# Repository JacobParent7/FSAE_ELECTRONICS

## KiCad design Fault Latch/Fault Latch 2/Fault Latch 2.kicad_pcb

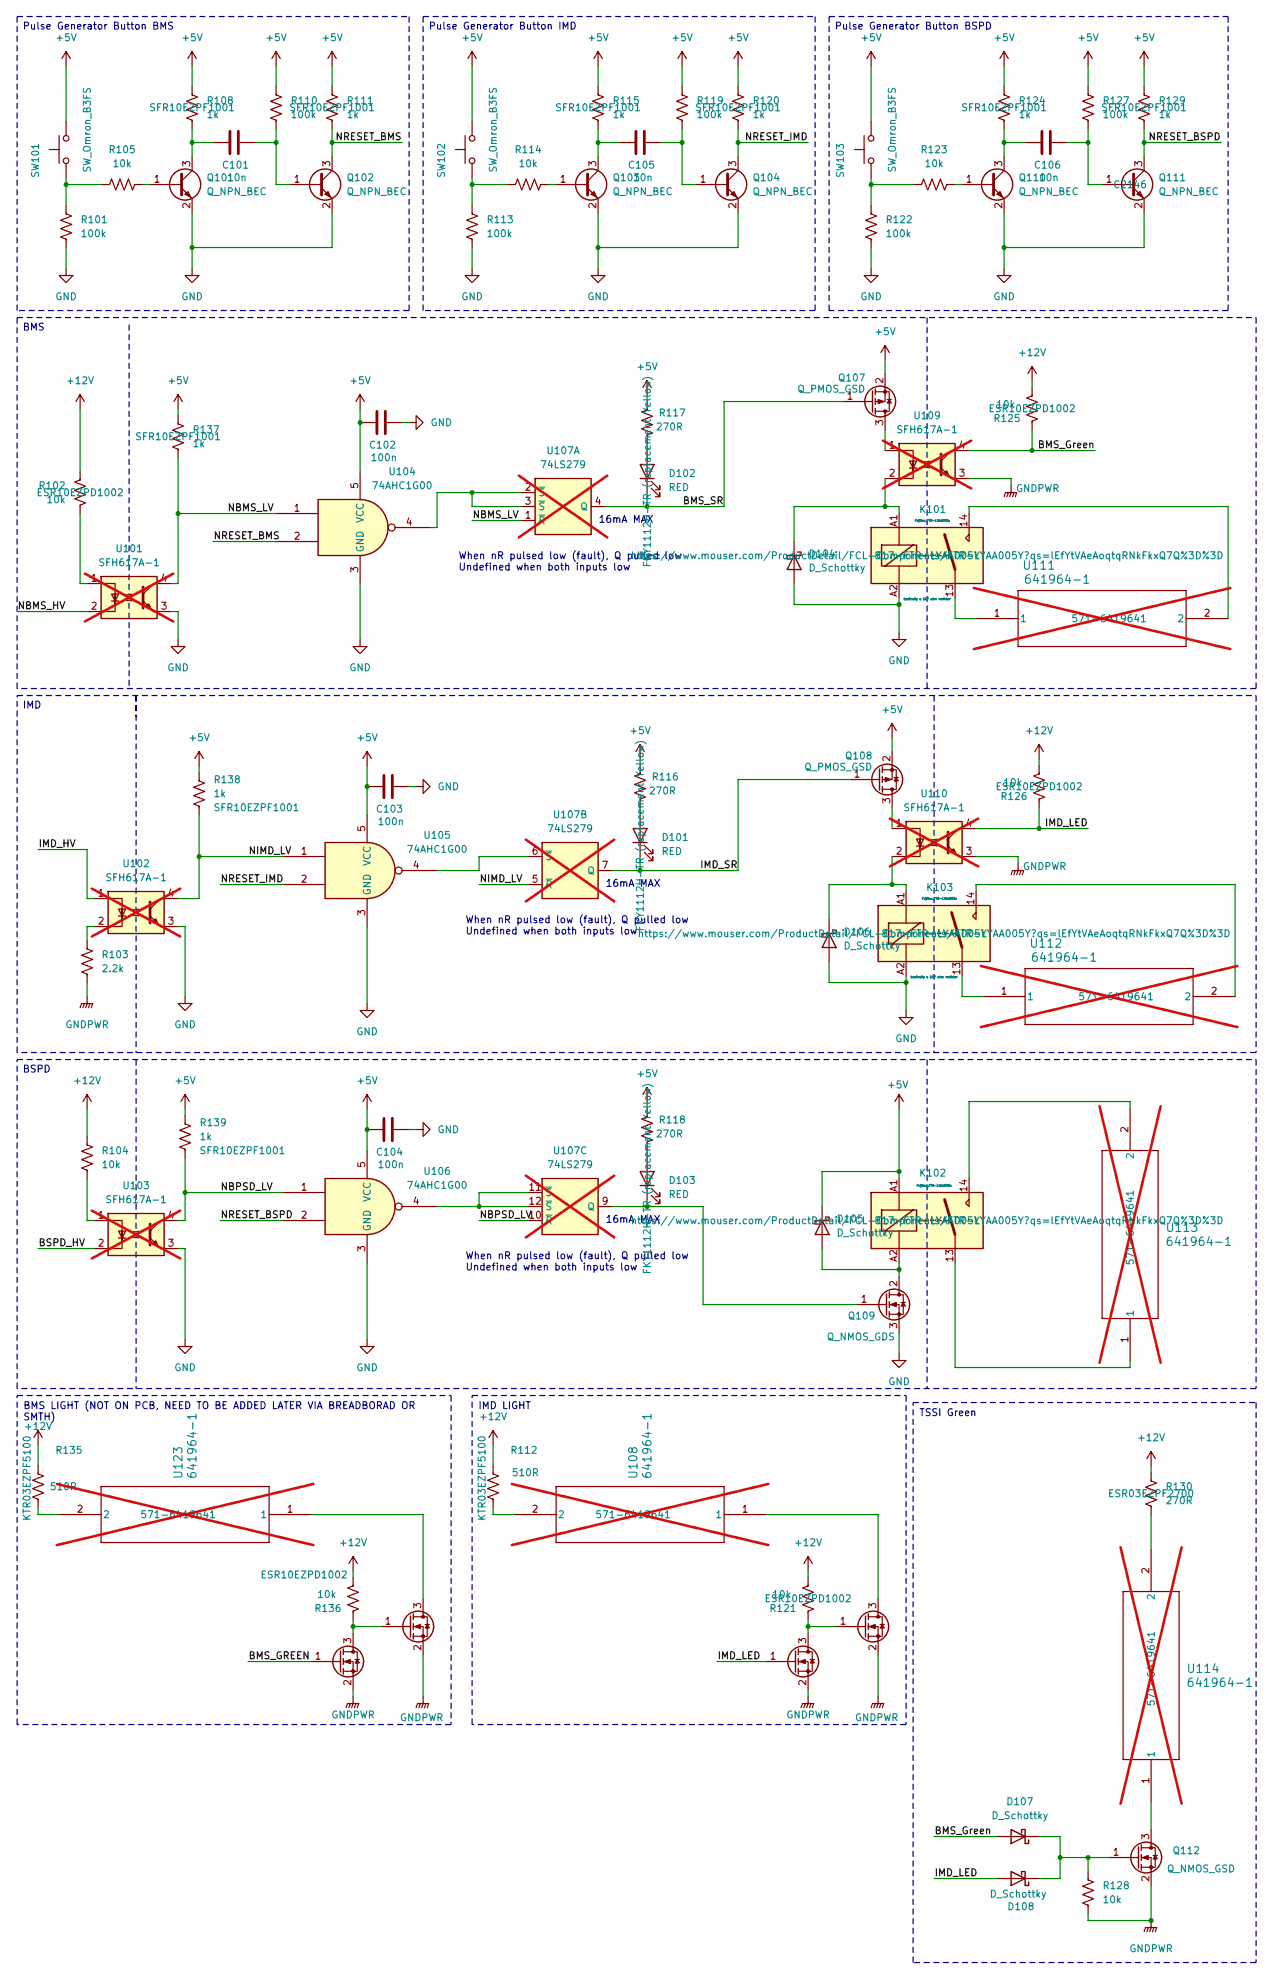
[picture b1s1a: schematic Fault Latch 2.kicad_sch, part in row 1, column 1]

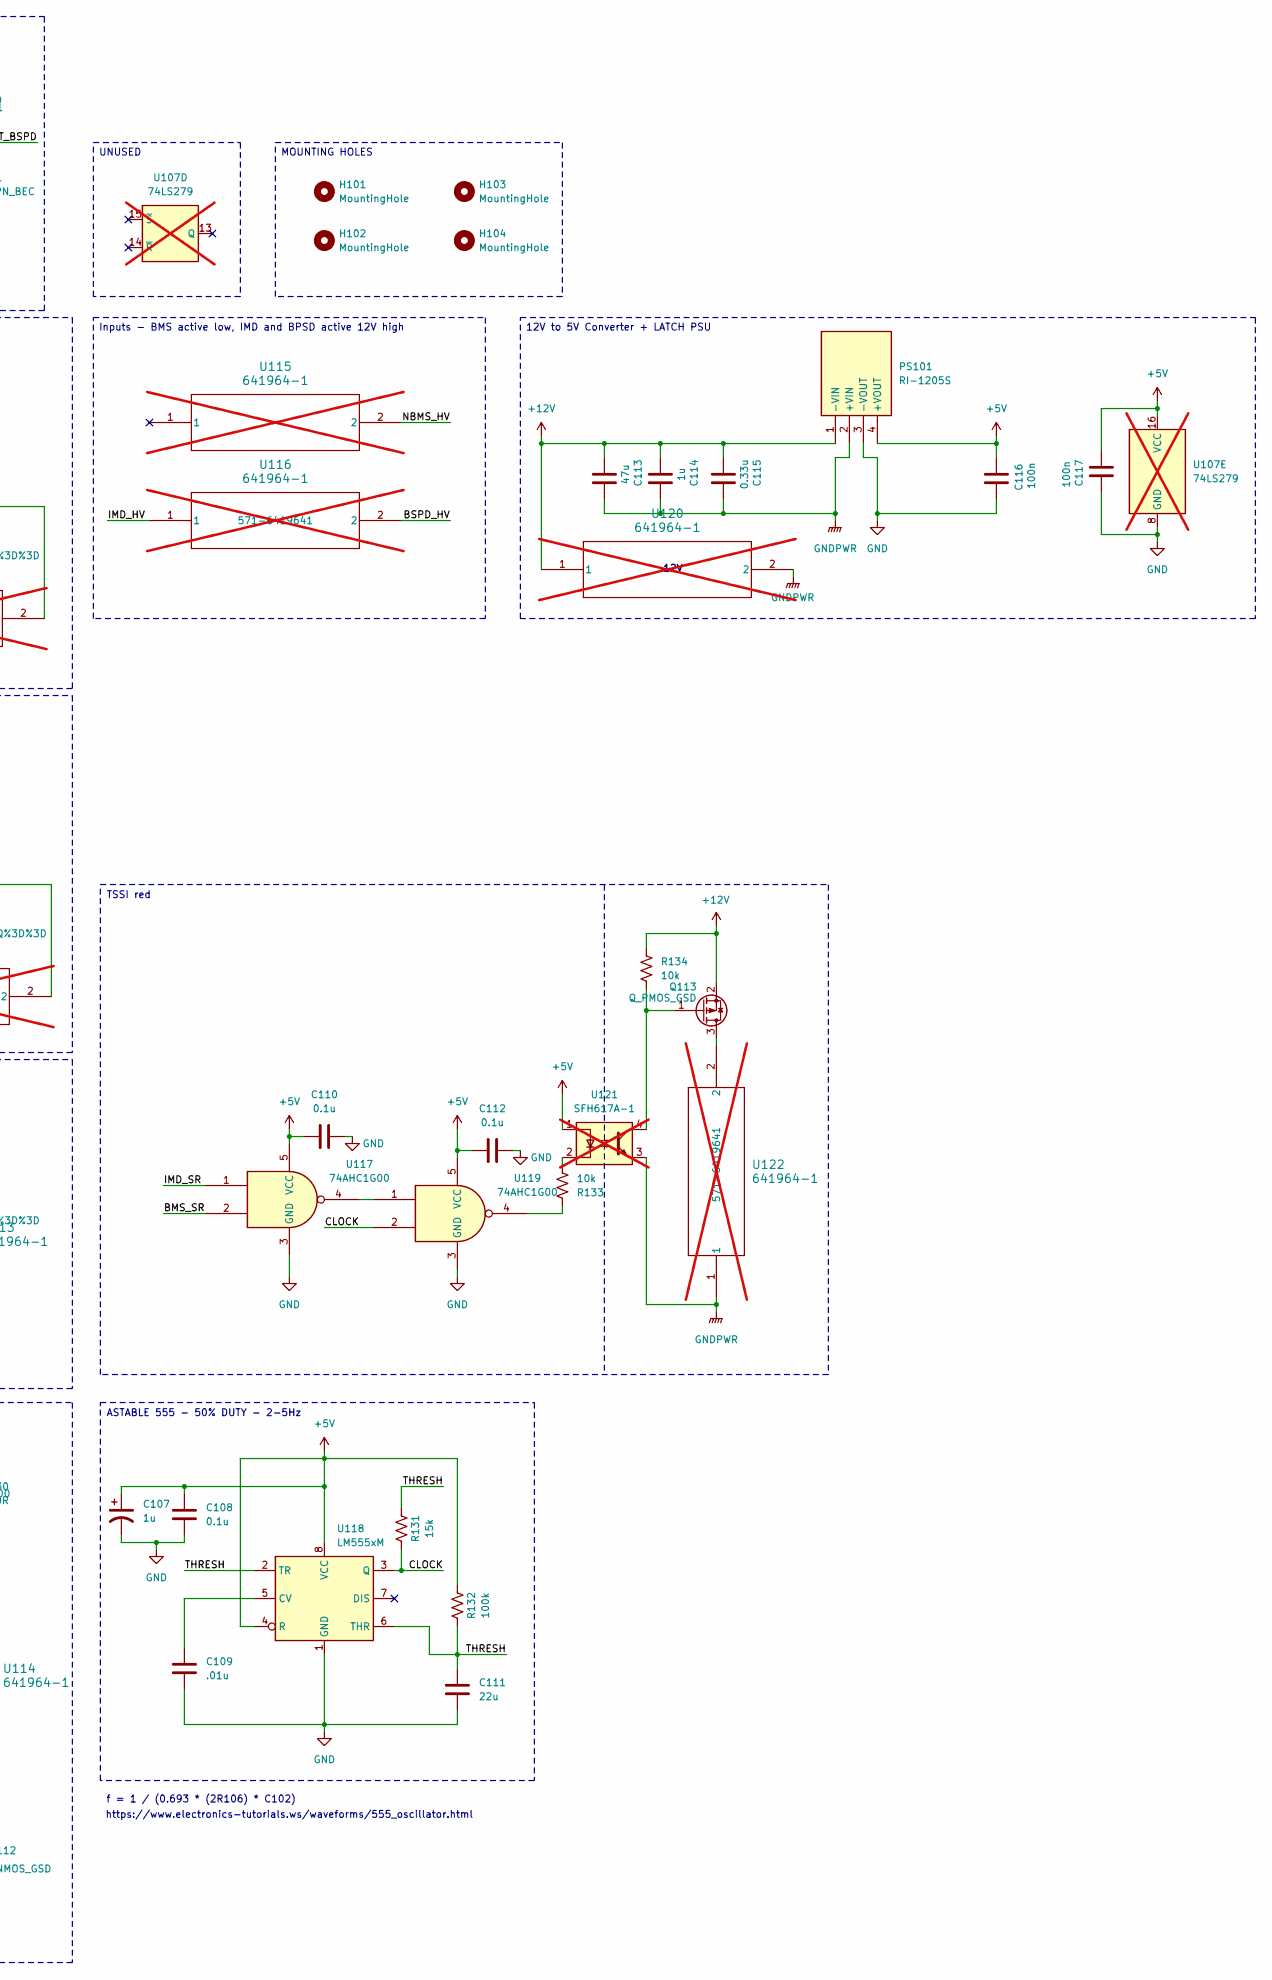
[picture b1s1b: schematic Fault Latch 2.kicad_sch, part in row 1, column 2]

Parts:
C101, C105, C106: 10n; C_0603_1608Metric_Pad1.08x0.95mm_HandSolder; JLC# C1589
C102, C103, C104, C116, C117: 100n; C_0603_1608Metric_Pad1.08x0.95mm_HandSolder; JLC# C1591
C107: 1u; C_0402_1005Metric; JLC# C59782
C108, C110, C112: 0.1u; C_0402_1005Metric; JLC# C133086
C109: .01u; C_0402_1005Metric; JLC# C15195
C111: 22u; C_0402_1005Metric; JLC# C105226
C113: 47u; CP_Elec_6.3x5.4; JLC# C2836440
C114: 1u; C_0805_2012Metric_Pad1.18x1.45mm_HandSolder; JLC# C91186
C115: 0.33u; C_0603_1608Metric_Pad1.08x0.95mm_HandSolder; JLC# C282682
D101, D102, D103: RED; LED_0805_2012Metric_Pad1.15x1.40mm_HandSolder; JLC# C19171391
D104, D105, D106, D107, D108: D_Schottky; D_SMA; JLC# C8678
H101, H102, H103, H104: MountingHole; MountingHole_3.2mm_M3
K101, K102, K103: Fujitsu_FTR-LYAA005x; Relay_SPST-NO_Fujitsu_FTR-LYAA005x_FormA_Vertical; MOUSER 817-FTR-LYAA005Y
PS101: RI-1205S; RI0505S; Mouser Part Number 919-RI-1205S
Q101, Q102, Q103, Q104, Q110, Q111: Q_NPN_BEC; SOT-23; JLC# C2146
Q105, Q106, Q112, Q114, Q115: Q_NMOS_GSD; SOT-23; JLC# C151421
Q107, Q108, Q113: Q_PMOS_GSD; SOT-523; JLC# C96676
Q109: Q_NMOS_GDS; TO-252-2; JLC# C2889156
R101, R110, R113, R119, R122, R127: 100k; R_0805_2012Metric_Pad1.20x1.40mm_HandSolder; JLC# C149504
R102, R121, R125, R126, R136: 10k; R_0805_2012Metric_Pad1.20x1.40mm_HandSolder; MOUSER ESR10EZPD1002
R103: 2.2k; R_0805_2012Metric_Pad1.20x1.40mm_HandSolder; JLC# C17520
R104, R105, R114, R123: 10k; R_0805_2012Metric_Pad1.20x1.40mm_HandSolder; JLC# C17414
R108, R111, R115, R120, R124, R129, R137, R138, R139: 1k; R_0805_2012Metric_Pad1.20x1.40mm_HandSolder; JLC# C17513
R112, R135: 510R; R_0603_1608Metric; MOUSER KTR03EZPF5100
R116, R117, R118: 270R; R_0805_2012Metric_Pad1.20x1.40mm_HandSolder; JLC# C17590
R128: 10k; R_0603_1608Metric; JLC# C130232
R130: 270R; R_0603_1608Metric; MOUSER ESR03EZPF2700
R131: 15k; R_0603_1608Metric; JLC# C22809
R132: 100k; R_0603_1608Metric; JLC# C60491
R133, R134: 10k; R_0603_1608Metric; JLC# C105637
SW101, SW102, SW103: SW_Omron_B3FS; SW_SPST_Omron_B3FS-100xP; JLC# C271750
U101, U102, U103, U109, U110, U121: SFH617A-1; DIP-4_W7.62mm; MOUSER SFH617A-1X007T; not fitted
U104, U105, U106, U117, U119: 74AHC1G00; SOT-23-5; JLC# C350556
U107: 74LS279; SOIC-16_3.9x9.9mm_P1.27mm; MOUSER 595-SN74LS279ADR; not fitted
U108, U111, U112, U113, U114, U115, U116, U120, U122, U123: 641964-1; TE_641964-1; MOUSER 571-6419641; not fitted
U118: LM555xM; SOIC-8_3.9x4.9mm_P1.27mm; JLC# C90760

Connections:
+5V: C102.1, C103.1, C104.1, C107.1, C108.1, C110.2, C112.2, C116.2, C117.1, D105.1 (K), K102.A1, PS101.4 (+VOUT), Q107.2 (S), Q108.2 (S), R108.1, R110.1, R111.1, R115.1, R116.2, R117.2, R118.2, R119.1, R120.1, R124.1, R127.1, R129.1, R132.2, R137.1, R138.2, R139.2, SW101.2, SW102.2, SW103.2, U104.5 (VCC), U105.5 (VCC), U106.5 (VCC), U107.16 (VCC), U117.5 (VCC), U118.4 (R), U118.8 (VCC), U119.5 (VCC), U121.1; also elsewhere on the board
+12V: C113.2, C114.2, C115.2, PS101.1 (-VIN), Q113.2 (S), R102.2, R104.2, R112.1, R121.1, R125.1, R126.1, R130.2, R134.1, R135.1, R136.1, U120.1
/BMS_Green: D107.2 (A), R125.2, U109.4
/BMS_SR: D102.1 (K), Q107.1 (G), U107.4 (Q), U117.2
/BSPD_HV: U103.2, U116.2
/CLOCK: R131.1, U118.3 (Q), U119.2
/IMD_HV: U102.1, U116.1
/IMD_LED: D108.2 (A), Q105.1 (G), R126.2, U110.4
/IMD_SR: D101.1 (K), Q108.1 (G), U107.7 (Q), U117.1
/NBMS_HV: U101.2, U115.2
/NBMS_LV: R137.2, U101.4, U104.1, U107.1 (~R); also elsewhere on the board
/NBPSD_LV: R139.1, U103.4, U106.1, U107.10 (~R); also elsewhere on the board
/NIMD_LV: R138.1, U102.4, U105.1, U107.5 (~R); also elsewhere on the board
/NRESET_BMS: Q102.3 (C), R111.2, U104.2
/NRESET_BSPD: Q111.3 (C), R129.2, U106.2
/NRESET_IMD: Q104.3 (C), R120.2, U105.2
/THRESH: C111.2, R131.2, R132.1, U118.2 (TR), U118.6 (THR)
GND: C102.2, C103.2, C104.2, C107.2, C108.2, C109.2, C110.1, C111.1, C112.1, C116.1, C117.2, D104.2 (A), D106.2 (A), K101.A2, K103.A2, PS101.3 (-VOUT), Q101.2 (E), Q102.2 (E), Q103.2 (E), Q104.2 (E), Q109.3 (S), Q110.2 (E), Q111.2 (E), R101.2, R113.2, R122.2, U101.3, U102.3, U103.3, U104.3 (GND), U105.3 (GND), U106.3 (GND), U107.8 (GND), U117.3 (GND), U118.1 (GND), U119.3 (GND)
GNDPWR: C113.1, C114.1, C115.1, PS101.2 (+VIN), Q105.2 (S), Q106.2 (S), Q112.2 (S), Q114.2 (S), Q115.2 (S), R103.2, R128.1, U109.3, U110.3, U120.2, U121.3, U122.1
unnamed: D101.2 (A), R116.1
unnamed: D102.2 (A), R117.1
unnamed: D103.2 (A), R118.1
unnamed: D103.1 (K), Q109.1 (G), U107.9 (Q)
unnamed: D104.1 (K), K101.A1, U109.2
unnamed: D105.2 (A), K102.A2, Q109.2 (D)
unnamed: D106.1 (K), K103.A1, U110.2
unnamed: D107.1 (K), D108.1 (K), Q112.1 (G), R128.2
unnamed: K101.13, U111.1
unnamed: K101.14, U111.2
unnamed: K102.13, U113.1
unnamed: K102.14, U113.2
unnamed: K103.13, U112.1
unnamed: K103.14, U112.2
unnamed: Q101.1 (B), R105.1
unnamed: C101.1, Q101.3 (C), R108.2
unnamed: C101.2, Q102.1 (B), R110.2
unnamed: Q103.1 (B), R114.1
unnamed: C105.1, Q103.3 (C), R115.2
unnamed: C105.2, Q104.1 (B), R119.2
unnamed: Q105.3 (D), Q106.1 (G), R121.2
unnamed: Q106.3 (D), U108.1
unnamed: Q107.3 (D), U109.1
unnamed: Q108.3 (D), U110.1
unnamed: Q110.1 (B), R123.1
unnamed: C106.1, Q110.3 (C), R124.2
unnamed: C106.2, Q111.1 (B), R127.2
unnamed: Q112.3 (D), U114.1
unnamed: Q113.3 (D), U122.2
unnamed: Q113.1 (G), R134.2, U121.4
unnamed: Q114.3 (D), Q115.1 (G), R136.2
unnamed: Q115.3 (D), U123.1
unnamed: R101.1, R105.2, SW101.1
unnamed: R102.1, U101.1
unnamed: R103.1, U102.2
unnamed: R104.1, U103.1
unnamed: R112.2, U108.2
unnamed: R113.1, R114.2, SW102.1
unnamed: R122.1, R123.2, SW103.1
unnamed: R130.1, U114.2
unnamed: R133.1, U121.2
unnamed: R133.2, U119.4
unnamed: R135.2, U123.2
unnamed: U104.4, U107.2 (~S), U107.3 (~S)
unnamed: U106.4, U107.11 (~S), U107.12 (~S)
unnamed: U105.4, U107.6 (~S)
unnamed: U117.4, U119.1
unnamed: C109.1, U118.5 (CV)

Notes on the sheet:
16mA MAX
12V
When nR pulsed low (fault), Q pulled low Undefined when both inputs low
f = 1 / (0.693 * (2R106) * C102)
https://www.electronics-tutorials.ws/waveforms/555_oscillator.html
UNUSED
BMS
Pulse Generator Button BMS
TSSI red
Pulse Generator Button BSPD
TSSI Green
ASTABLE 555 - 50% DUTY - 2-5Hz
Pulse Generator Button IMD
12V to 5V Converter + LATCH PSU
MOUNTING HOLES
Inputs - BMS active low, IMD and BPSD active 12V high
BMS LIGHT (NOT ON PCB, NEED TO BE ADDED LATER VIA BREADBORAD OR SMTH)
IMD
BSPD
IMD LIGHT

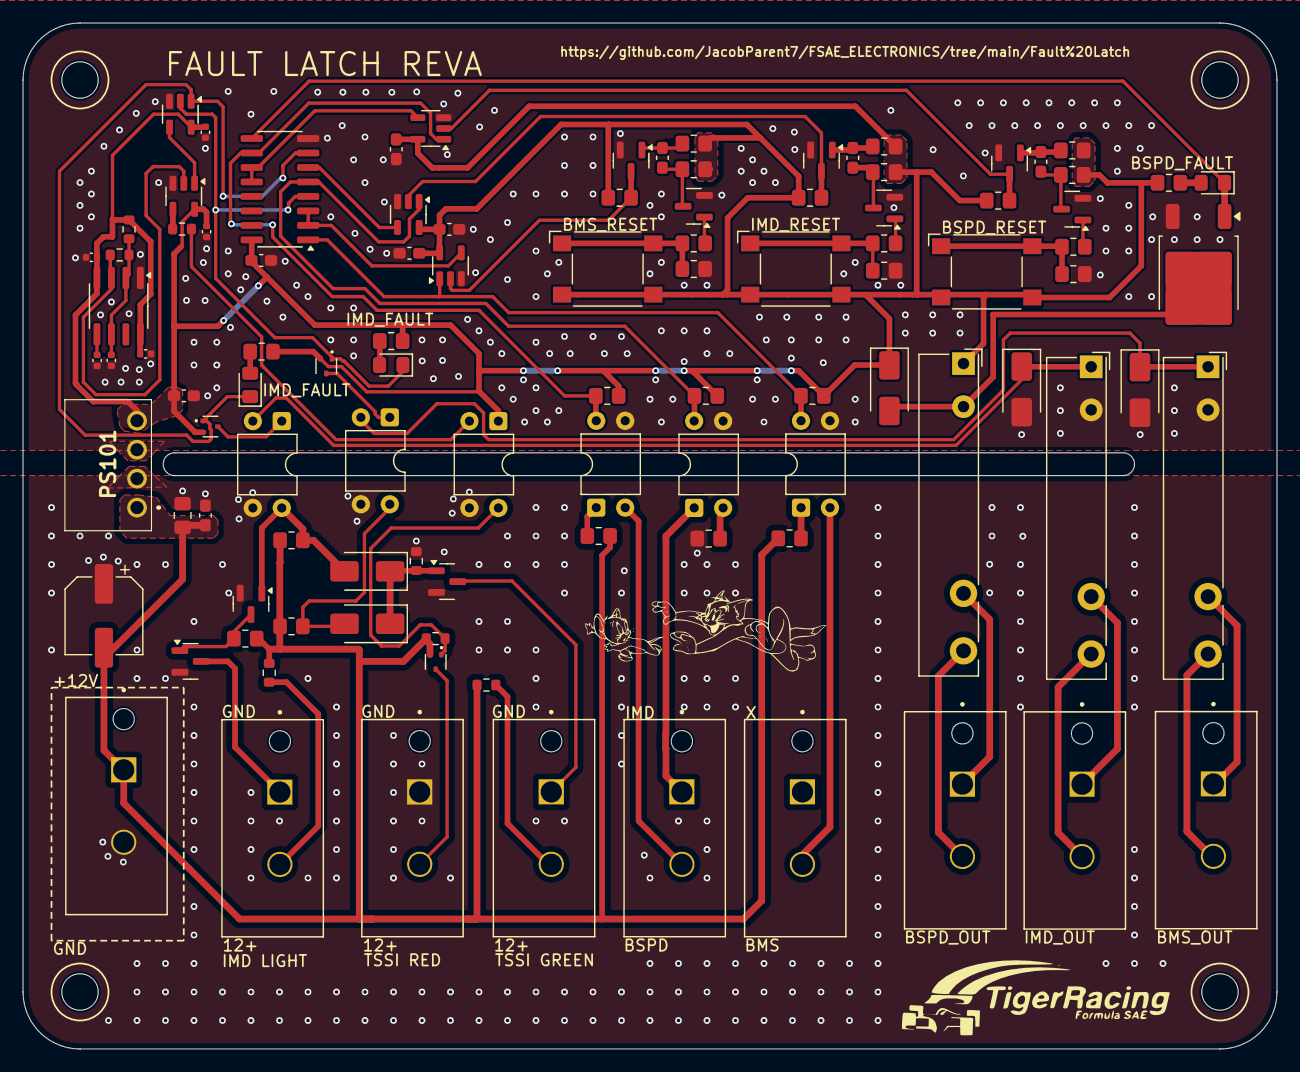
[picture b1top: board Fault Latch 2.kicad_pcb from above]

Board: 2 copper layers, 110.0 x 90.0 mm, 105 parts (0 on the bottom side), 64 nets.

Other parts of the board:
R106, R107, R109: 10k; R_0805_2012Metric_Pad1.20x1.40mm_HandSolder

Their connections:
+5V: R106.1, R107.1, R109.1; also elsewhere on the board
/NBMS_LV: R106.2; also elsewhere on the board
/NBPSD_LV: R107.2; also elsewhere on the board
/NIMD_LV: R109.2; also elsewhere on the board

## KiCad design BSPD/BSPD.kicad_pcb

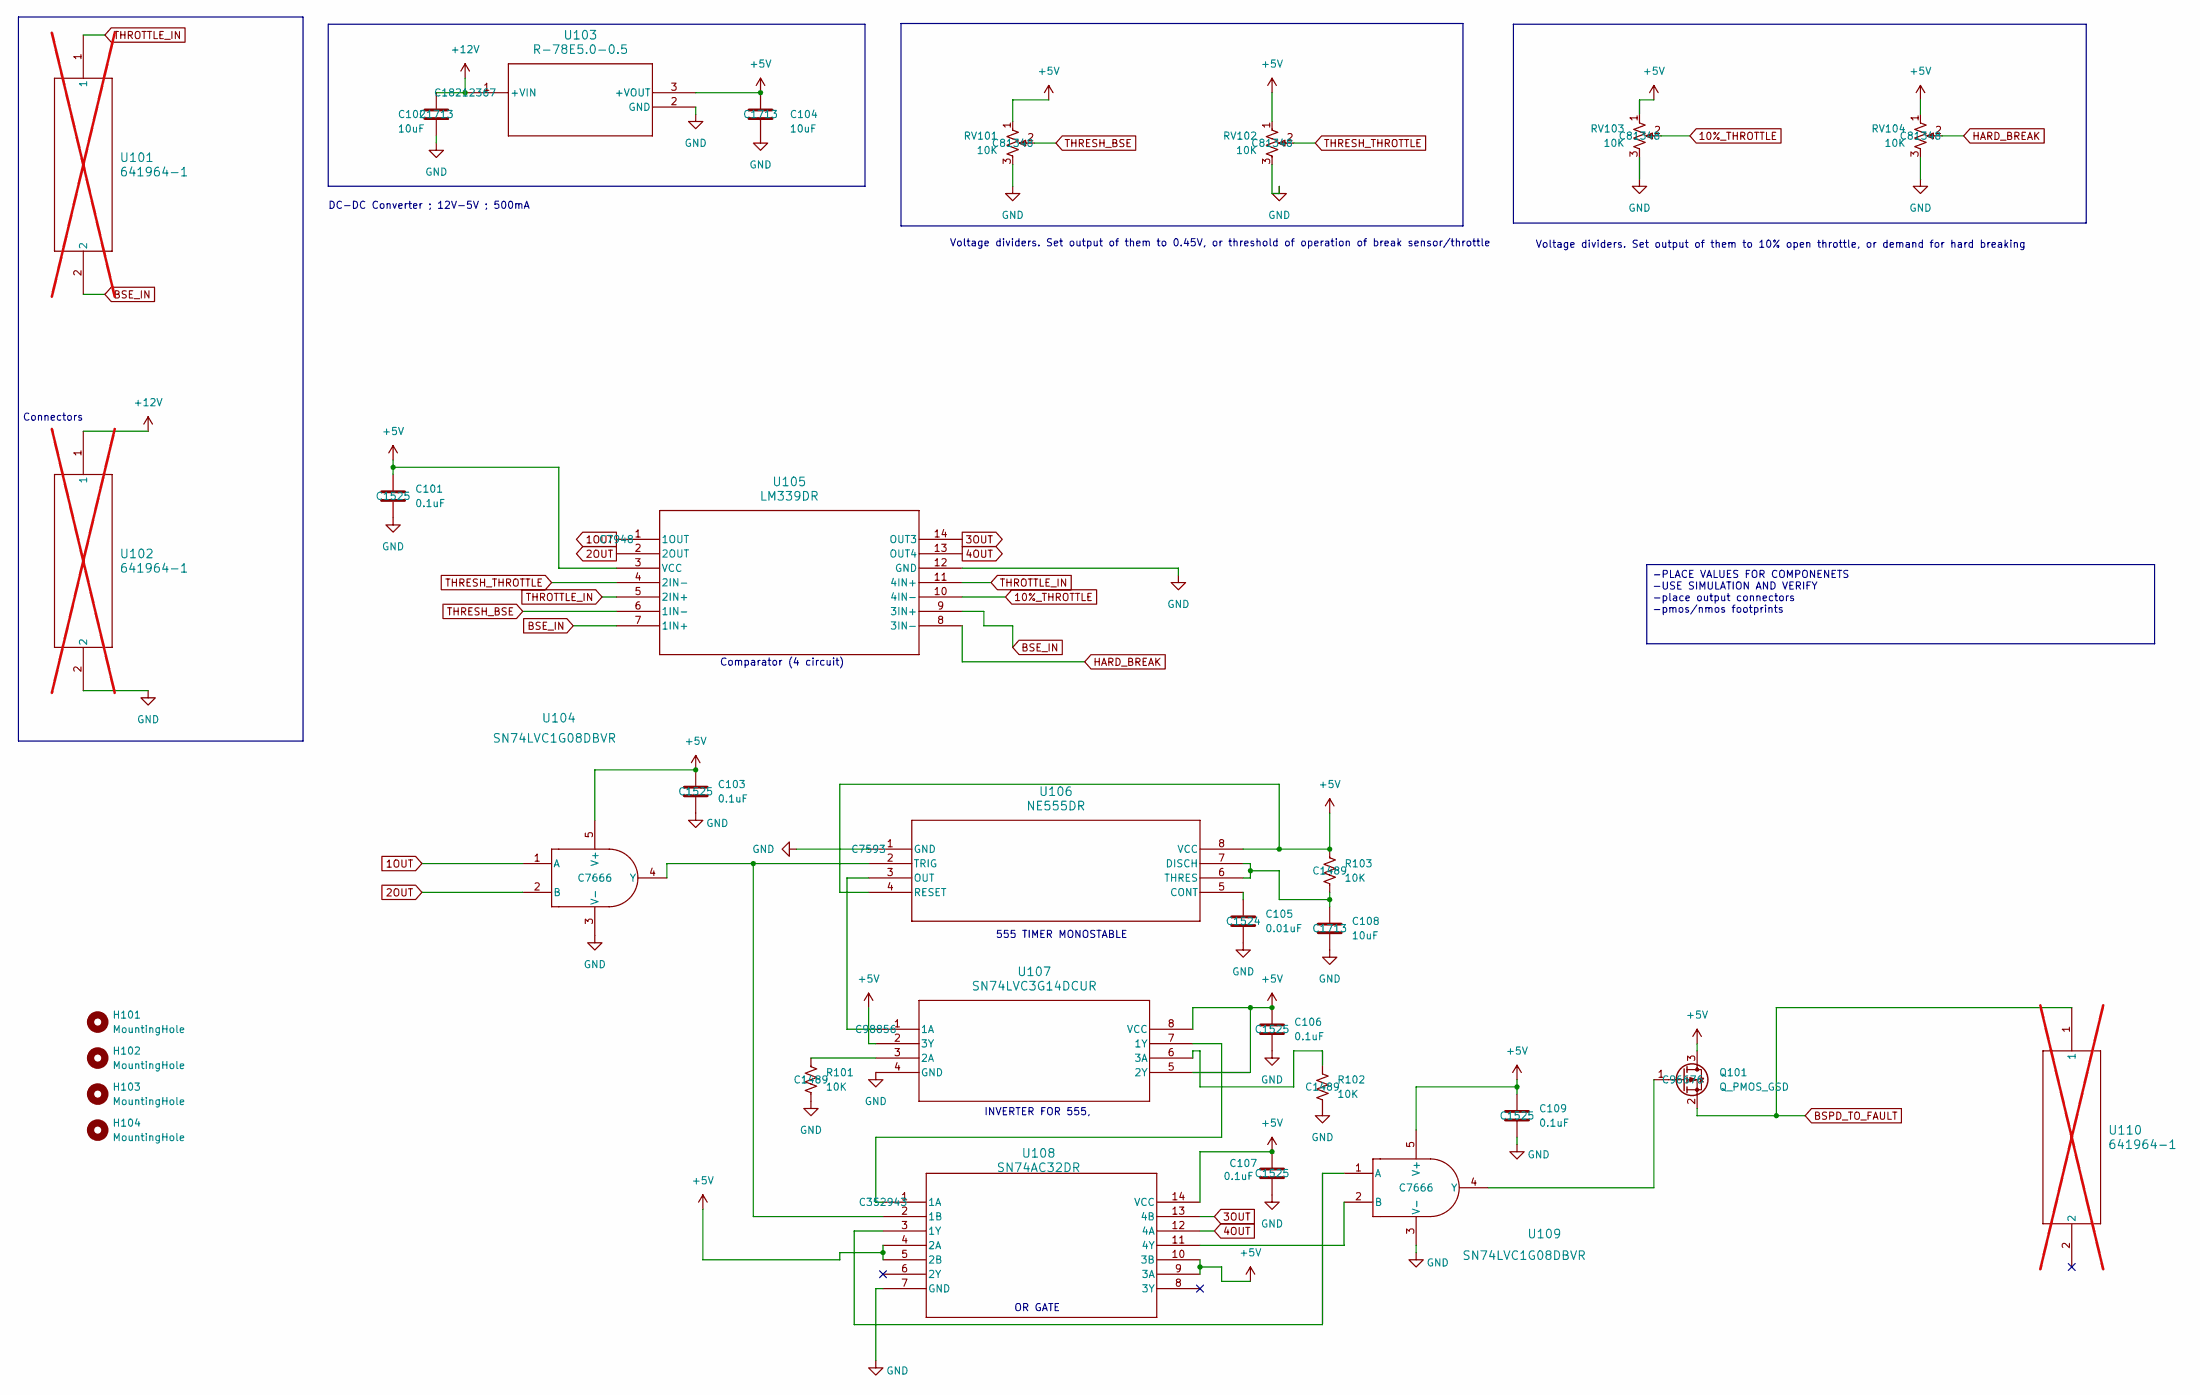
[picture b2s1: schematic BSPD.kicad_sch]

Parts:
C101, C103, C106, C107, C109: 0.1uF; C_0402_1005Metric; JLCPCB Part # C1525
C102, C104, C108: 10uF; C_0805_2012Metric; JLCPCB Part # C1713
C105: 0.01uF; C_0402_1005Metric; JLCPCB Part # C1524
H101, H102, H103, H104: MountingHole; MountingHole_2.2mm_M2
Q101: Q_PMOS_GSD; SOT-523; JLCPCB Part # C96676
R101, R102, R103: 10K; R_1206_3216Metric; JLCPCB Part # C1489
RV101, RV102, RV103, RV104: 10K; POT_3224W; JLCPCB Part # C81348
U101, U102, U110: 641964-1; 641964-1_TYC; not fitted
U103: R-78E5.0-0.5; R-78E-0.5_RCP; JLCPCB Part # C18212367
U104, U109: SN74LVC1G08DBVR; DBV0005A_L; JLCPCB Part # C7666
U105: LM339DR; D14; JLCPCB Part # C7948
U106: NE555DR; D8; JLCPCB Part # C7593
U107: SN74LVC3G14DCUR; DCU8_TEX; JLCPCB Part # C98856
U108: SN74AC32DR; D14; JLCPCB Part # C352943

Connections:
1OUT: U104.1 (A), U105.1 (1OUT)
2OUT: U104.2 (B), U105.2 (2OUT)
3OUT: U105.14 (OUT3), U108.13 (4B)
4OUT: U105.13 (OUT4), U108.12 (4A)
10%_THROTTLE: RV103.2, U105.10 (4IN-)
+5V: C101.1, C103.1, C104.1, C106.1, C107.1, C109.1, Q101.3 (D), R103.1, RV101.1, RV102.1, RV103.1, RV104.1, U103.3 (+VOUT), U104.5 (V+), U105.3 (VCC), U106.4 (RESET), U106.8 (VCC), U107.2 (3Y), U107.5 (2Y), U107.8 (VCC), U108.4 (2A), U108.5 (2B), U108.9 (3A), U108.10 (3B), U108.14 (VCC), U109.5 (V+)
+12V: C102.1, U102.1, U103.1 (+VIN)
BSE_IN: U101.2, U105.7 (1IN+), U105.9 (3IN+)
BSPD_TO_FAULT: Q101.2 (S), U110.1
GND: C101.2, C102.2, C103.2, C104.2, C105.2, C106.2, C107.2, C108.2, C109.2, R101.2, R102.2, RV101.3, RV102.3, RV103.3, RV104.3, U102.2, U103.2 (GND), U104.3 (V-), U105.12 (GND), U106.1 (GND), U107.4 (GND), U108.7 (GND), U109.3 (V-)
HARD_BREAK: RV104.2, U105.8 (3IN-)
unnamed: Q101.1 (G), U109.4 (Y)
unnamed: U104.4 (Y), U106.2 (TRIG), U108.2 (1B)
unnamed: C105.1, U106.5 (CONT)
unnamed: C108.1, R103.2, U106.6 (THRES), U106.7 (DISCH)
unnamed: U106.3 (OUT), U107.1 (1A)
unnamed: U107.7 (1Y), U108.1 (1A)
unnamed: R101.1, U107.3 (2A)
unnamed: R102.1, U107.6 (3A)
unnamed: U108.3 (1Y), U109.1 (A)
unnamed: U108.11 (4Y), U109.2 (B)
THRESH_BSE: RV101.2, U105.6 (1IN-)
THRESH_THROTTLE: RV102.2, U105.4 (2IN-)
THROTTLE_IN: U101.1, U105.5 (2IN+), U105.11 (4IN+)

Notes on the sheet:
Comparator (4 circuit)
OR GATE
Voltage dividers. Set output of them to 10% open throttle, or demand for hard breaking
Voltage dividers. Set output of them to 0.45V, or threshold of operation of break sensor/throttle
INVERTER FOR 555,
555 TIMER MONOSTABLE
DC-DC Converter ; 12V-5V ; 500mA
Connectors
-PLACE VALUES FOR COMPONENETS -USE SIMULATION AND VERIFY -place output connectors -pmos/nmos footprints

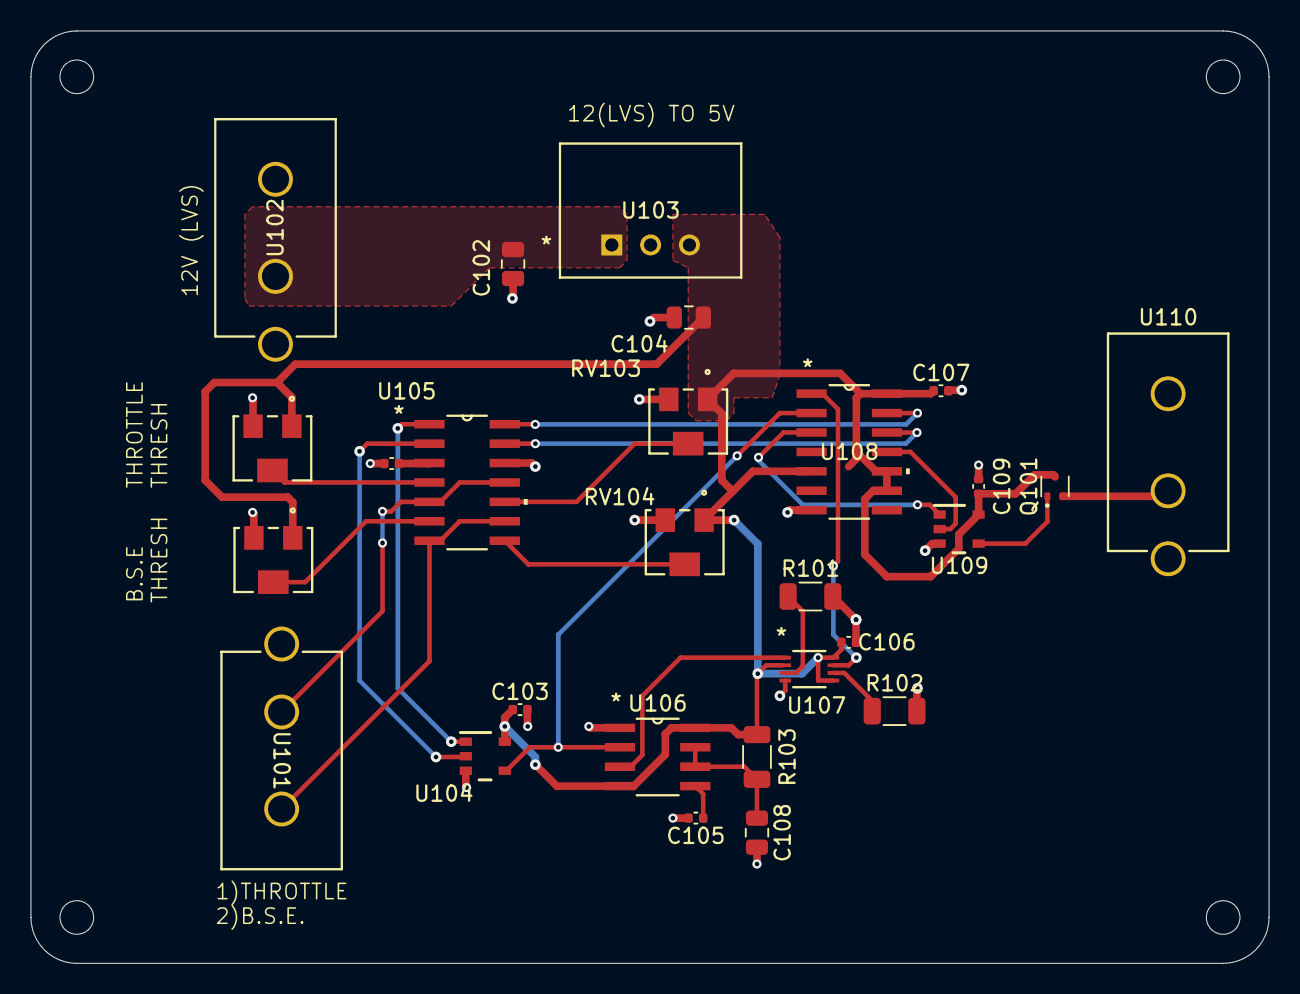
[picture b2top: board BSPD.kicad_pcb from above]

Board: 2 copper layers, 81.0 x 61.0 mm, 31 parts (0 on the bottom side), 24 nets.

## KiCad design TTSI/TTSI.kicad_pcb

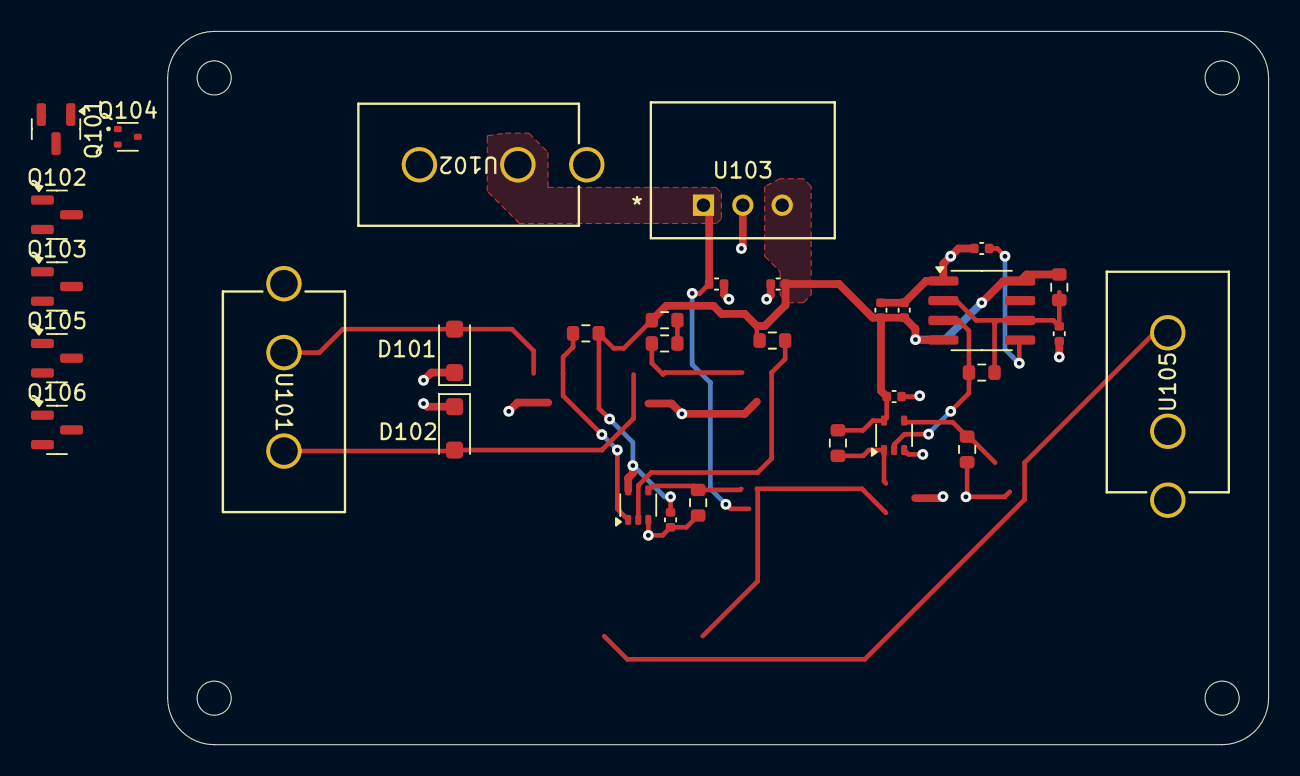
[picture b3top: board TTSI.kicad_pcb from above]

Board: 2 copper layers, 71.0 x 46.0 mm, 36 parts (0 on the bottom side), 17 nets.

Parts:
C101, C102: 10uF; C_0402_1005Metric
C103, C105, C107: 0.1u; C_0402_1005Metric
C104: 1u; C_0402_1005Metric
C106: .01u; C_0402_1005Metric
C108: 22u; C_0402_1005Metric
D101, D102: D_TVS; D_SOD-123F
D103: RED; R_0603_1608Metric
H101, H102, H103, H104: MountingHole; MountingHole_2.2mm_M2
Q101, Q102, Q103, Q105, Q106: Q_NMOS_GSD; SOT-23
Q104: Q_PMOS_GSD; SOT-523
R101, R103, R105: 10k; R_0603_1608Metric
R102: 500R; R_0603_1608Metric
R104, R106: 1k; R_0603_1608Metric
R107: 15k; R_0603_1608Metric
R108: 100k; R_0603_1608Metric
U101, U102, U105: 641964-1; 641964-1_TYC
U103: R-78E5.0-0.5; R-78E-0.5_RCP
U104: 74AHC1G32; SOT-353_SC-70-5
U106: 74AHC1G08; SOT-353_SC-70-5
U107: LM555xM; SOIC-8_3.9x4.9mm_P1.27mm

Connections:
+5V: C102.1, C103.1, C104.1, C105.1, C107.1, R101.1, R102.1, R103.1, R105.1, R108.2, U103.3 (OUT), U104.5 (VCC), U106.5 (VCC), U107.4 (R), U107.8 (VCC)
+12V: C101.1, Q104.3 (D), U102.1, U103.1 (IN)
/BMS_LV: Q101.3 (D), R101.2, U104.1
/CLOCK: R107.1, U106.2, U107.3 (Q)
/IMD_LV: Q103.3 (D), R103.2, U104.2
/THRESH: C108.2, R107.2, R108.1, U107.2 (TR), U107.6 (THR)
BMS_HV: D101.2 (A2), Q101.1 (G), U101.1
GND: C101.2, C102.2, C103.2, C104.2, C105.2, C106.2, C107.2, C108.1, D101.1 (A1), D102.1 (A1), Q101.2 (S), Q102.2 (S), Q103.2 (S), Q105.2 (S), Q106.2 (S), R104.2, R106.2, U102.2, U103.2 (GND), U104.3 (GND), U106.3 (GND), U107.1 (GND)
IMD_HV: D102.2 (A2), Q102.1 (G), U101.2
unnamed: D103.2 (A), R102.2
unnamed: D103.1 (K), Q102.3 (D), Q103.1 (G)
unnamed: Q104.1 (G), R104.1, U104.4
unnamed: Q104.2 (S), Q105.1 (G), U105.1
unnamed: Q105.3 (D), R105.2, U106.1
unnamed: Q106.3 (D), U105.2
unnamed: Q106.1 (G), R106.1, U106.4
unnamed: C106.1, U107.5 (CV)

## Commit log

2025-02-15 Validated Fault Latch on falstad LTspice online, and make basic RML sketch
2025-04-16 Fixes to BSPD
2025-07-16 Fixed errors on schematic. Need to update pcb layout
2025-12-03 Created using Colab
